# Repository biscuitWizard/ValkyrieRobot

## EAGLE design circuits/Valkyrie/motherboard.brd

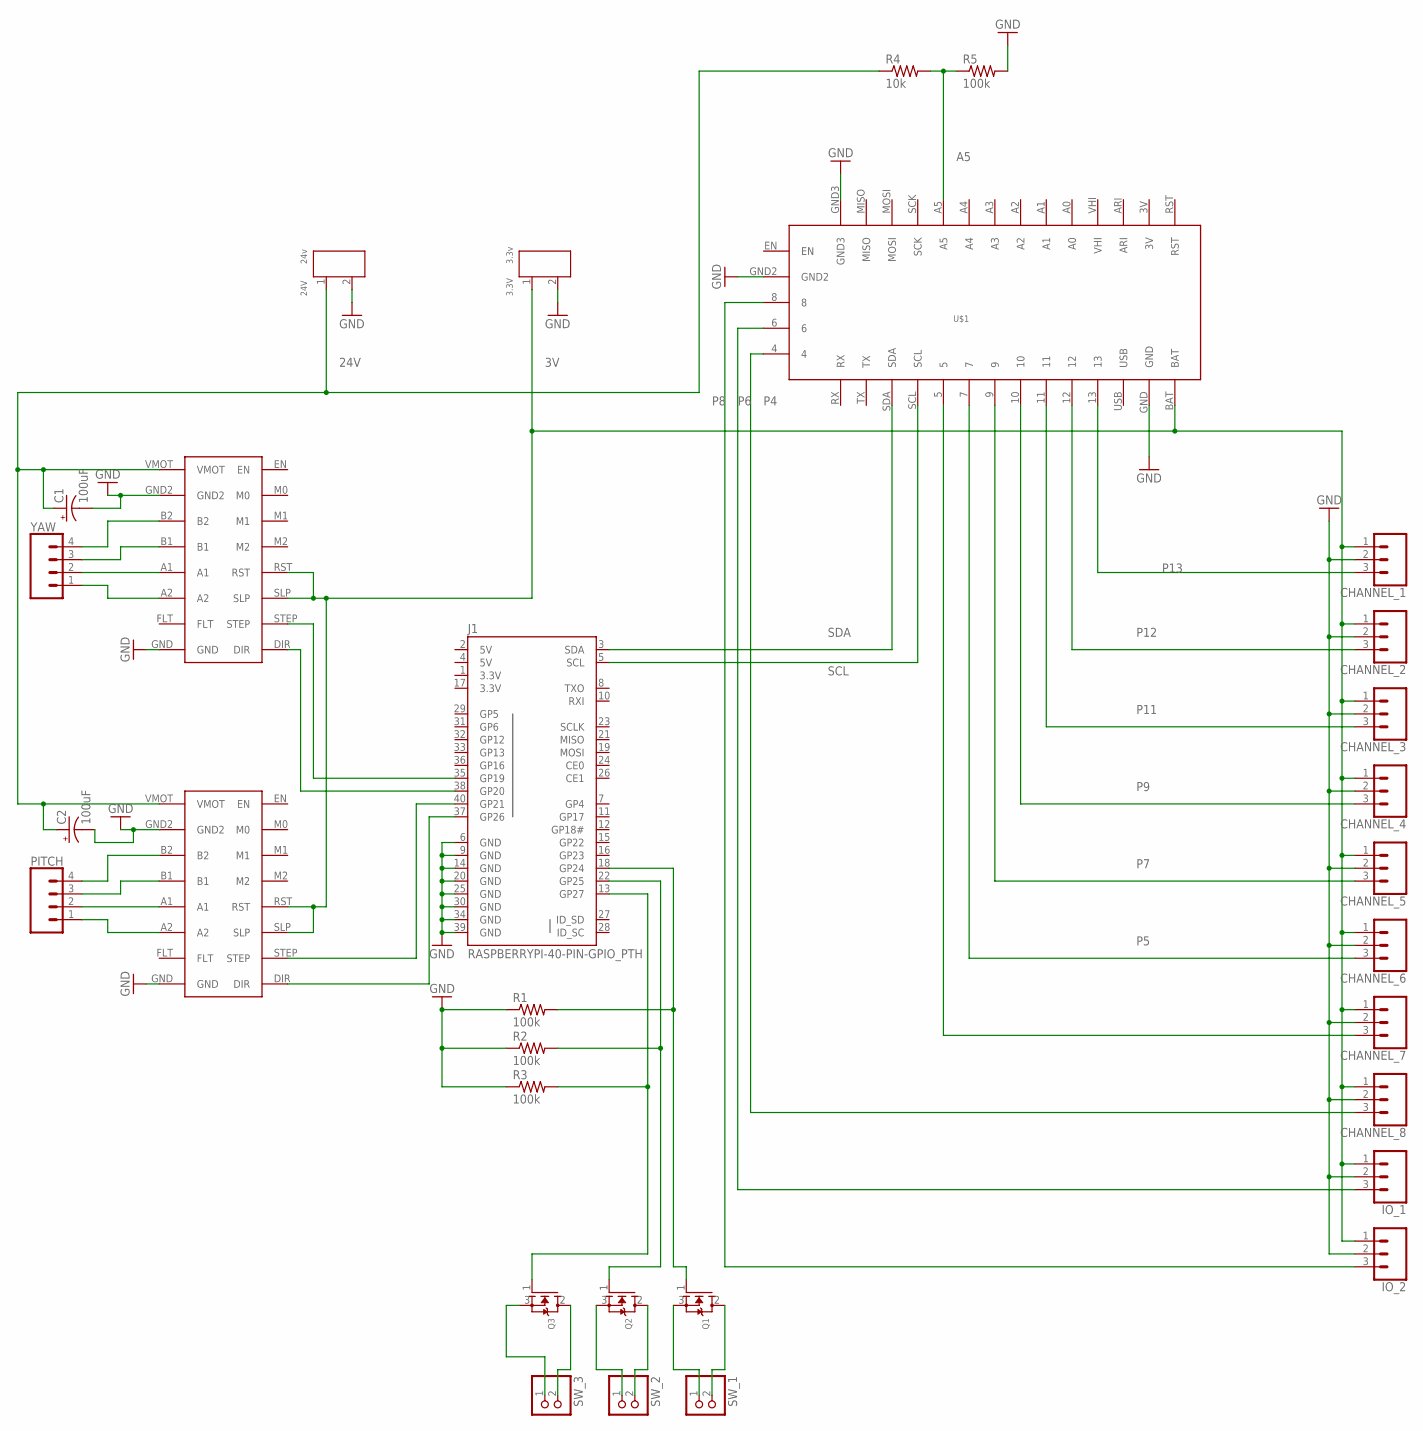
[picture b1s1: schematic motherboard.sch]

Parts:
3.3V: 3.3v; H2-5.0-10.5X8.0MM
24V: 24v; H2-5.0-10.5X8.0MM
C1, C2: 100uF; CPOL-RADIAL-5MM-10MM
CHANNEL_1, CHANNEL_2, CHANNEL_3, CHANNEL_4, CHANNEL_5, CHANNEL_6, CHANNEL_7, CHANNEL_8: CONN_03JST-PTH; JST-3-PTH
IO_1, IO_2: CONN_03JST-PTH; JST-3-PTH
J1: RASPBERRYPI-40-PIN-GPIO_PTH; 2X20_SHROUDED
PITCH: CONN_04JST-PTH; JST-4-PTH
Q1, Q2, Q3: MOSFET-NGDS_TO220V; TO220V
R1, R2, R3, R5: 100k; 0207/2V
R4: 10k; 0207/2V
SW_1, SW_2, SW_3: JST_2PIN-THM-RA; JST-PH-2-THM-RA
U$1: ITSY_BITSY
U$3, U$4: STEPPER_DRIVER
YAW: CONN_04JST-PTH; JST-4-PTH

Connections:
3.3V: J1.1 (3.3V), J1.17 (3.3V)
3V: 3.3V.1, CHANNEL_1.1, CHANNEL_2.1, CHANNEL_3.1, CHANNEL_4.1, CHANNEL_5.1, CHANNEL_6.1, CHANNEL_7.1, CHANNEL_8.1, IO_1.1, IO_2.1, U$1.BAT, U$3.RST, U$3.SLP, U$4.RST, U$4.SLP
5V: J1.2 (5V), J1.4 (5V)
24V: 24V.1, C1.+, C2.+, R4.1, U$3.VMOT, U$4.VMOT
A5: R4.2, R5.1, U$1.A5
GND: 3.3V.2, 24V.2, C1.-, C2.-, CHANNEL_1.2, CHANNEL_2.2, CHANNEL_3.2, CHANNEL_4.2, CHANNEL_5.2, CHANNEL_6.2, CHANNEL_7.2, CHANNEL_8.2, IO_1.2, IO_2.2, J1.6 (GND), J1.9 (GND), J1.14 (GND), J1.20 (GND), J1.25 (GND), J1.30 (GND), J1.34 (GND), J1.39 (GND), R1.1, R2.1, R3.1, R5.2, U$1.GND, U$1.GND2, U$1.GND3, U$3.GND, U$3.GND2, U$4.GND2
unnamed: CHANNEL_7.3, U$1.5
unnamed: J1.13 (GP27), Q3.1 (G), R3.2
unnamed: J1.22 (GP25), Q2.1 (G), R2.2
unnamed: J1.18 (GP24), Q1.1 (G), R1.2
unnamed: J1.37 (GP26), U$4.DIR
unnamed: Q3.3 (S), SW_3.1 (2)
unnamed: Q3.2 (D), SW_3.2 (1)
unnamed: Q2.3 (S), SW_2.1 (2)
unnamed: Q2.2 (D), SW_2.2 (1)
unnamed: Q1.3 (S), SW_1.1 (2)
unnamed: Q1.2 (D), SW_1.2 (1)
unnamed: J1.40 (GP21), U$4.STEP
unnamed: J1.38 (GP20), U$3.DIR
unnamed: J1.35 (GP19), U$3.STEP
unnamed: U$3.B2, YAW.4
unnamed: U$3.A2, YAW.1
unnamed: U$3.A1, YAW.2
unnamed: U$3.B1, YAW.3
unnamed: PITCH.4, U$4.B2
unnamed: PITCH.3, U$4.B1
unnamed: PITCH.2, U$4.A1
unnamed: PITCH.1, U$4.A2
P4: CHANNEL_8.3, U$1.4
P5: CHANNEL_6.3, U$1.7
P6: IO_1.3, U$1.6
P7: CHANNEL_5.3, U$1.9
P8: IO_2.3, U$1.8
P9: CHANNEL_4.3, U$1.10
P11: CHANNEL_3.3, U$1.11
P12: CHANNEL_2.3, U$1.12
P13: CHANNEL_1.3, U$1.13
SCL: J1.5 (SCL), U$1.SCL
SDA: J1.3 (SDA), U$1.SDA

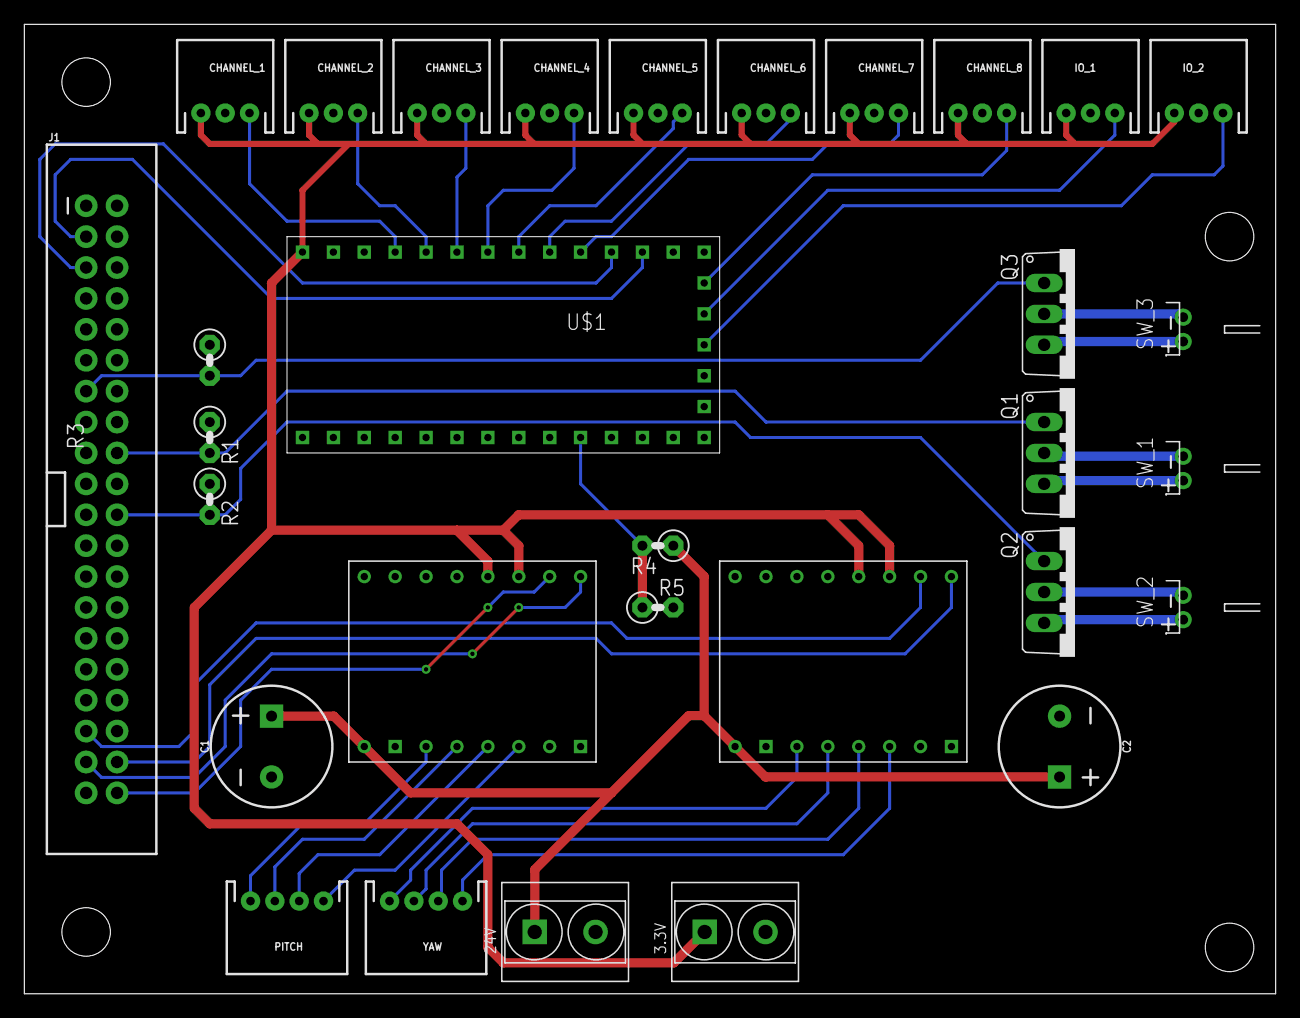
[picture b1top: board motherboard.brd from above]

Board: 2 copper layers, 102.8 x 79.7 mm, 31 parts (0 on the bottom side), 39 nets.

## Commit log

2019-09-24 Adding motherboard files.
2019-09-24 Adding ADC Slave file.
2019-10-11 Adding a bunch of files. Whatever.
2019-10-14 Adding program for raspberry pi control code.
2019-10-14 Adding MCU Radio sketch for Arduino
2019-10-16 Adding many py files to master controller.
2019-10-16 Adding forgotten config paramter.
2019-10-16 Adding channel mappings.
2019-10-16 Fixing config error & an infinite while loop.
2019-10-16 Fixing key not found error.
2019-10-16 Fixing throttle error math.
2019-10-16 Added ESC calibration and arming.
2019-10-16 fixing some whitespace
2019-10-16 Removing unneeded definitions.
2019-10-16 Decreasing framerate.
2019-10-16 Giving radio an easier timeout to finish writing to the serial buffer.
2019-10-16 Adding start and loop for mcu.
2019-10-16 Fixing arming procedure to not happen twice and fixing dict association for motor mappings.
2019-10-22 Updated main program to have some command line reporting and support.
2019-10-22 Built mcu_radio with latest revision for Due.
2019-10-22 Adding more config options and slowign framerate to 5.
2019-10-23 Repairs to program and radio for conversion to short from byte array, adding in serial terminator.
2019-10-25 Fixing struct unpack to 2 bytes.
2019-10-25 Removing channel overrun debug message.
2019-10-25 Updated how the radio serializes data.
2019-10-25 Adding string decode to radio.
2019-10-25 Adding some more type safety and input verification from the channel provider.
2019-10-25 Upgrades to radio.
2019-10-25 Updating encoding and adding universal try-catch for stability.
2019-10-25 Adding exception information to main loop.
2019-10-25 Cleaning up some decoding errors in serial.
2019-10-25 Reverting debug changes to main program loop.
2019-10-25 Flushing USB serial buffer before reading now.
2019-10-25 Fixing data truncation bug in serial interface.
2019-10-25 Filling out the MCU and adding debug info.
2019-10-25 Removing trycatch from main loop. Obscuring too many bugs.
2019-10-25 Quick test.
2019-10-25 Making some other things work in the MCU.
2019-10-25 Adding some more helpful debug info.
2019-10-25 Fixing string error.
2019-10-25 Adding more debug info to controller calculations.
2019-10-25 Fixing config to channel assignments.
2019-10-25 Continuous drive motors are now live.
2019-10-25 Updating some of the throttle modifiers.

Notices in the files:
parts and their libraries:
SparkFun-Capacitors: Licensing: Creative Commons ShareAlike 4.0 International - https://creativecommons.org/licenses/by-sa/4.0
